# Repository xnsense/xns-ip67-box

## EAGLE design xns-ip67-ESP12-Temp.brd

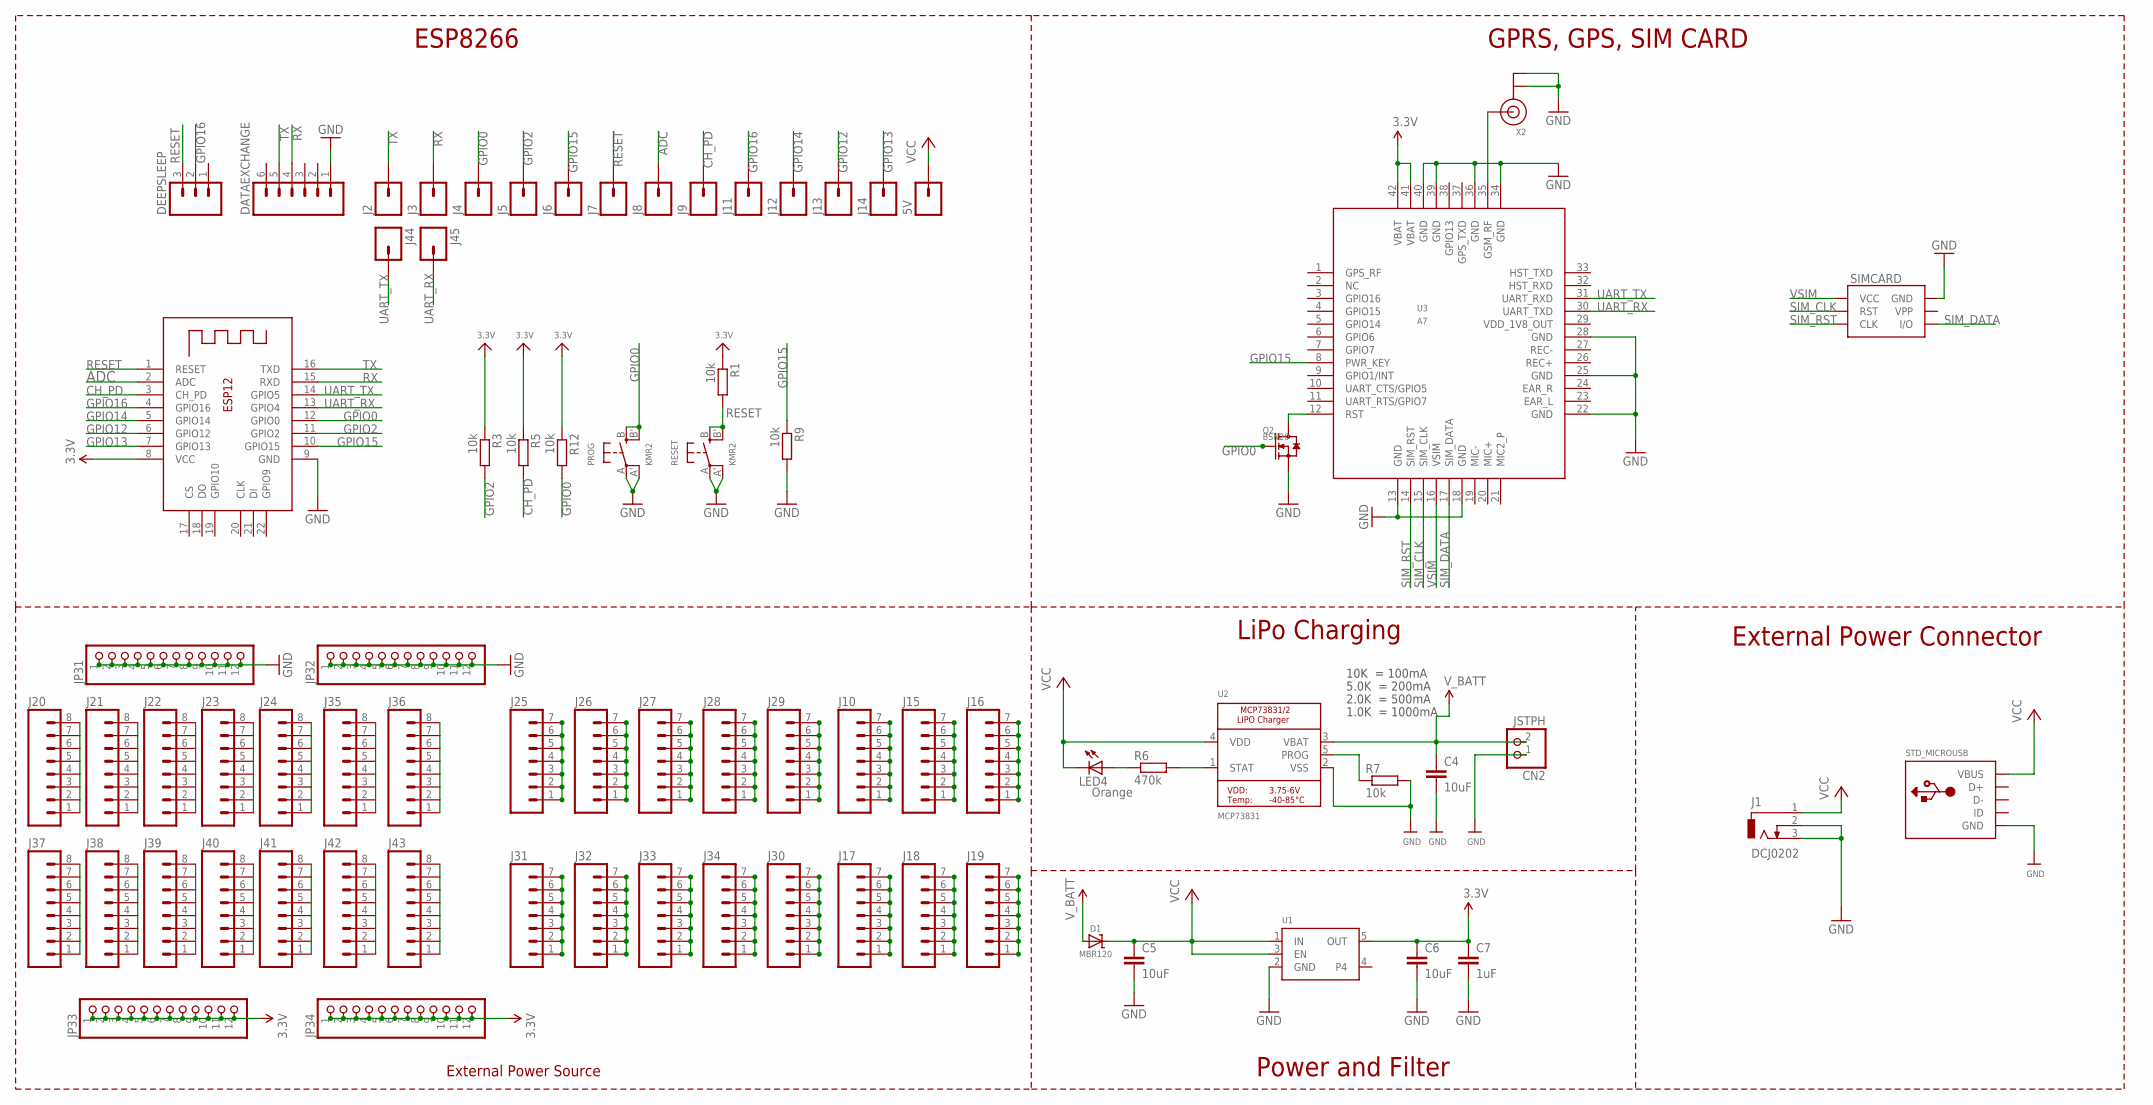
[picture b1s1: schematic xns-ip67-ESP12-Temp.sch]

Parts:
5V: M01NOSILK-KIT; 1X01NS-KIT
C4, C5, C6: 10uF; C2.5-2
C7: 1uF; C2.5-2
CN2: JSTPH; JSTPH2
D1: MBR120; SOD-123
DATAEXCHANGE: M06FEMALE_LOCK; 1X06_FEMALE_LOCK.010
DEEPSLEEP: M031X03_NO_SILK; 1X03_NO_SILK
J1: DCJ0202
J2, J3, J4, J5, J6, J7, J8, J9, J11, J12, J13, J14, J44, J45: M01NOSILK-KIT; 1X01NS-KIT
J10, J15, J16, J17, J18, J19, J25, J26, J27, J28, J29, J30, J31, J32, J33, J34: M07NO_SILK; 1X07_NO_SILK
J20, J21, J22, J23, J24, J35, J36, J37, J38, J39, J40, J41, J42, J43: M08NO_SILK_FEMALE_PTH; 1X08_NO_SILK
JP31, JP32, JP33, JP34: HEADER-1X12; 1X12_ROUND
LED4: Orange; LED5MM
PROG: KMR2; BTN_KMR2_4.6X2.8
Q2: BSN20; SOT23@1
R1, R3, R5, R7, R9, R12: 10k; 0204/7
R6: 470k; 0204/7
RESET: KMR2; BTN_KMR2_4.6X2.8
SIMCARD: SIMHOLDERSIM; SIMHOLDER
STD_MICROUSB: USB_MICRO_20329_V2; 4UCONN_20329_V2
U1: VREG_SOT23-5; SOT23-5
U2: MCP73831; SOT23-5@1
U3: A7
X1: ESP-12E
X2: ANTENNA_U.FL; U.FL

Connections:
3.3V: C6.1, C7.1, JP33.1, JP33.2, JP33.3, JP33.4, JP33.5, JP33.6, JP33.7, JP33.8, JP33.9, JP33.10, JP33.11, JP33.12, JP34.1, JP34.2, JP34.3, JP34.4, JP34.5, JP34.6, JP34.7, JP34.8, JP34.9, JP34.10, JP34.11, JP34.12, R1.1, R3.1, R5.1, R12.1, U1.5 (OUT), U3.41 (VBAT), U3.42 (VBAT), X1.8 (VCC)
ADC: J8.1, X1.2 (ADC)
CH_PD: J9.1, R5.2, X1.3 (CH_PD)
GND: C4.2, C5.2, C6.2, C7.2, CN2.1, DATAEXCHANGE.1, J1.2, J1.3, JP31.1, JP31.2, JP31.3, JP31.4, JP31.5, JP31.6, JP31.7, JP31.8, JP31.9, JP31.10, JP31.11, JP31.12, JP32.1, JP32.2, JP32.3, JP32.4, JP32.5, JP32.6, JP32.7, JP32.8, JP32.9, JP32.10, JP32.11, JP32.12, PROG.A, PROG.A' (P1), Q2.2 (S), R7.2, R9.2, RESET.A, RESET.A' (P1), SIMCARD.C5 (GND), STD_MICROUSB.BASE@1 (GND), STD_MICROUSB.BASE@2 (GND), STD_MICROUSB.GND, STD_MICROUSB.SPRT@1 (GND), STD_MICROUSB.SPRT@2 (GND), STD_MICROUSB.SPRT@3 (GND), STD_MICROUSB.SPRT@4 (GND), U1.2 (GND), U2.2 (VSS), U3.13 (GND), U3.18 (GND), U3.22 (GND), U3.25 (GND), U3.28 (GND), U3.34 (GND), U3.36 (GND), U3.39 (GND), U3.40 (GND), X1.9 (GND), X2.1 (GND), X2.2 (GND)
GPIO0: J4.1, PROG.B (S), PROG.B' (S1), Q2.1 (G), R12.2, X1.12 (GPIO0)
GPIO2: J5.1, R3.2, X1.11 (GPIO2)
GPIO12: J13.1, X1.6 (GPIO12)
GPIO13: J14.1, X1.7 (GPIO13)
GPIO14: J12.1, X1.5 (GPIO14)
GPIO15: J6.1, R9.1, U3.8 (PWR_KEY), X1.10 (GPIO15)
GPIO16: DEEPSLEEP.2, J11.1, X1.4 (GPIO16)
unnamed: J20.1, J20.2, J20.3, J20.4, J20.5, J20.6, J20.7, J20.8
unnamed: J21.1, J21.2, J21.3, J21.4, J21.5, J21.6, J21.7, J21.8
unnamed: U3.35 (GSM_RF), X2.3 (SIGNAL)
unnamed: J22.1, J22.2, J22.3, J22.4, J22.5, J22.6, J22.7, J22.8
unnamed: J23.1, J23.2, J23.3, J23.4, J23.5, J23.6, J23.7, J23.8
unnamed: J24.1, J24.2, J24.3, J24.4, J24.5, J24.6, J24.7, J24.8
unnamed: J35.1, J35.2, J35.3, J35.4, J35.5, J35.6, J35.7, J35.8
unnamed: J37.1, J37.2, J37.3, J37.4, J37.5, J37.6, J37.7, J37.8
unnamed: J38.1, J38.2, J38.3, J38.4, J38.5, J38.6, J38.7, J38.8
unnamed: J39.1, J39.2, J39.3, J39.4, J39.5, J39.6, J39.7, J39.8
unnamed: J40.1, J40.2, J40.3, J40.4, J40.5, J40.6, J40.7, J40.8
unnamed: J10.1, J10.2, J10.3, J10.4, J10.5, J10.6, J10.7
unnamed: J41.1, J41.2, J41.3, J41.4, J41.5, J41.6, J41.7, J41.8
unnamed: J15.1, J15.2, J15.3, J15.4, J15.5, J15.6, J15.7
unnamed: J16.1, J16.2, J16.3, J16.4, J16.5, J16.6, J16.7
unnamed: J17.1, J17.2, J17.3, J17.4, J17.5, J17.6, J17.7
unnamed: J18.1, J18.2, J18.3, J18.4, J18.5, J18.6, J18.7
unnamed: J19.1, J19.2, J19.3, J19.4, J19.5, J19.6, J19.7
unnamed: J42.1, J42.2, J42.3, J42.4, J42.5, J42.6, J42.7, J42.8
unnamed: J36.1, J36.2, J36.3, J36.4, J36.5, J36.6, J36.7, J36.8
unnamed: J43.1, J43.2, J43.3, J43.4, J43.5, J43.6, J43.7, J43.8
unnamed: R7.1, U2.5 (PROG)
unnamed: J31.1, J31.2, J31.3, J31.4, J31.5, J31.6, J31.7
unnamed: J32.1, J32.2, J32.3, J32.4, J32.5, J32.6, J32.7
unnamed: R6.2, U2.1 (STAT)
unnamed: J33.1, J33.2, J33.3, J33.4, J33.5, J33.6, J33.7
unnamed: J34.1, J34.2, J34.3, J34.4, J34.5, J34.6, J34.7
unnamed: LED4.A, R6.1
unnamed: J25.1, J25.2, J25.3, J25.4, J25.5, J25.6, J25.7
unnamed: J26.1, J26.2, J26.3, J26.4, J26.5, J26.6, J26.7
unnamed: J27.1, J27.2, J27.3, J27.4, J27.5, J27.6, J27.7
unnamed: J28.1, J28.2, J28.3, J28.4, J28.5, J28.6, J28.7
unnamed: J29.1, J29.2, J29.3, J29.4, J29.5, J29.6, J29.7
unnamed: J30.1, J30.2, J30.3, J30.4, J30.5, J30.6, J30.7
RESET: DEEPSLEEP.3, J7.1, R1.2, RESET.B (S), RESET.B' (S1), X1.1 (RESET)
RESET_KEY: Q2.3 (D), U3.12 (RST)
RX: DATAEXCHANGE.4, J3.1, X1.15 (RXD)
SIM_CLK: SIMCARD.C2 (RST), U3.15 (SIM_CLK)
SIM_DATA: SIMCARD.C7 (I/O), U3.17 (SIM_DATA)
SIM_RST: SIMCARD.C3 (CLK), U3.14 (SIM_RST)
TX: DATAEXCHANGE.5, J2.1, X1.16 (TXD)
UART_RX: J45.1, U3.30 (UART_TXD), X1.13 (GPIO4)
UART_TX: J44.1, U3.31 (UART_RXD), X1.14 (GPIO5)
VCC: 5V.1, C5.1, D1.C, J1.1, LED4.K (C), STD_MICROUSB.VBUS, U1.1 (IN), U1.3 (EN), U2.4 (VDD)
VSIM: SIMCARD.C1 (VCC), U3.16 (VSIM)
V_BATT: C4.1, CN2.2, D1.A, U2.3 (VBAT)

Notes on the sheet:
10K = 100mA
5.0K = 200mA
2.0K = 500mA
1.0K = 1000mA
External Power Connector
LiPo Charging
Power and Filter
GPRS, GPS, SIM CARD
ESP8266
External Power Source

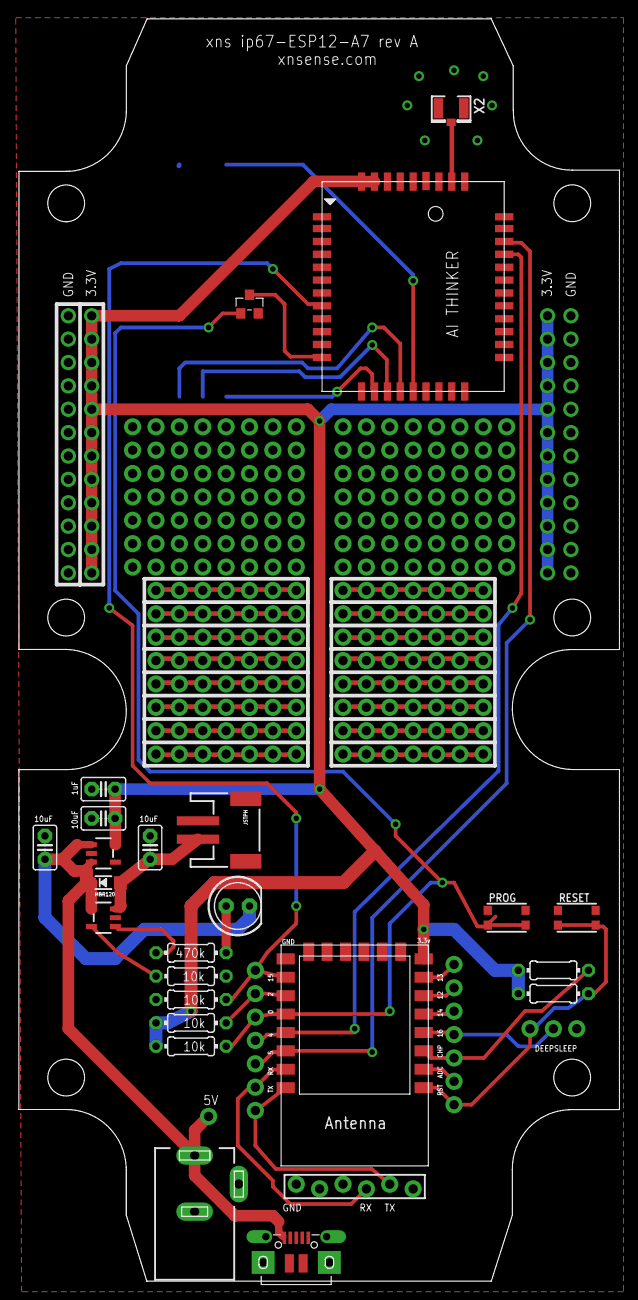
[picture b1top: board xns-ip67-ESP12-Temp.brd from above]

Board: 2 copper layers, 65.3 x 137.2 mm, 76 parts (1 on the bottom side), 57 nets.

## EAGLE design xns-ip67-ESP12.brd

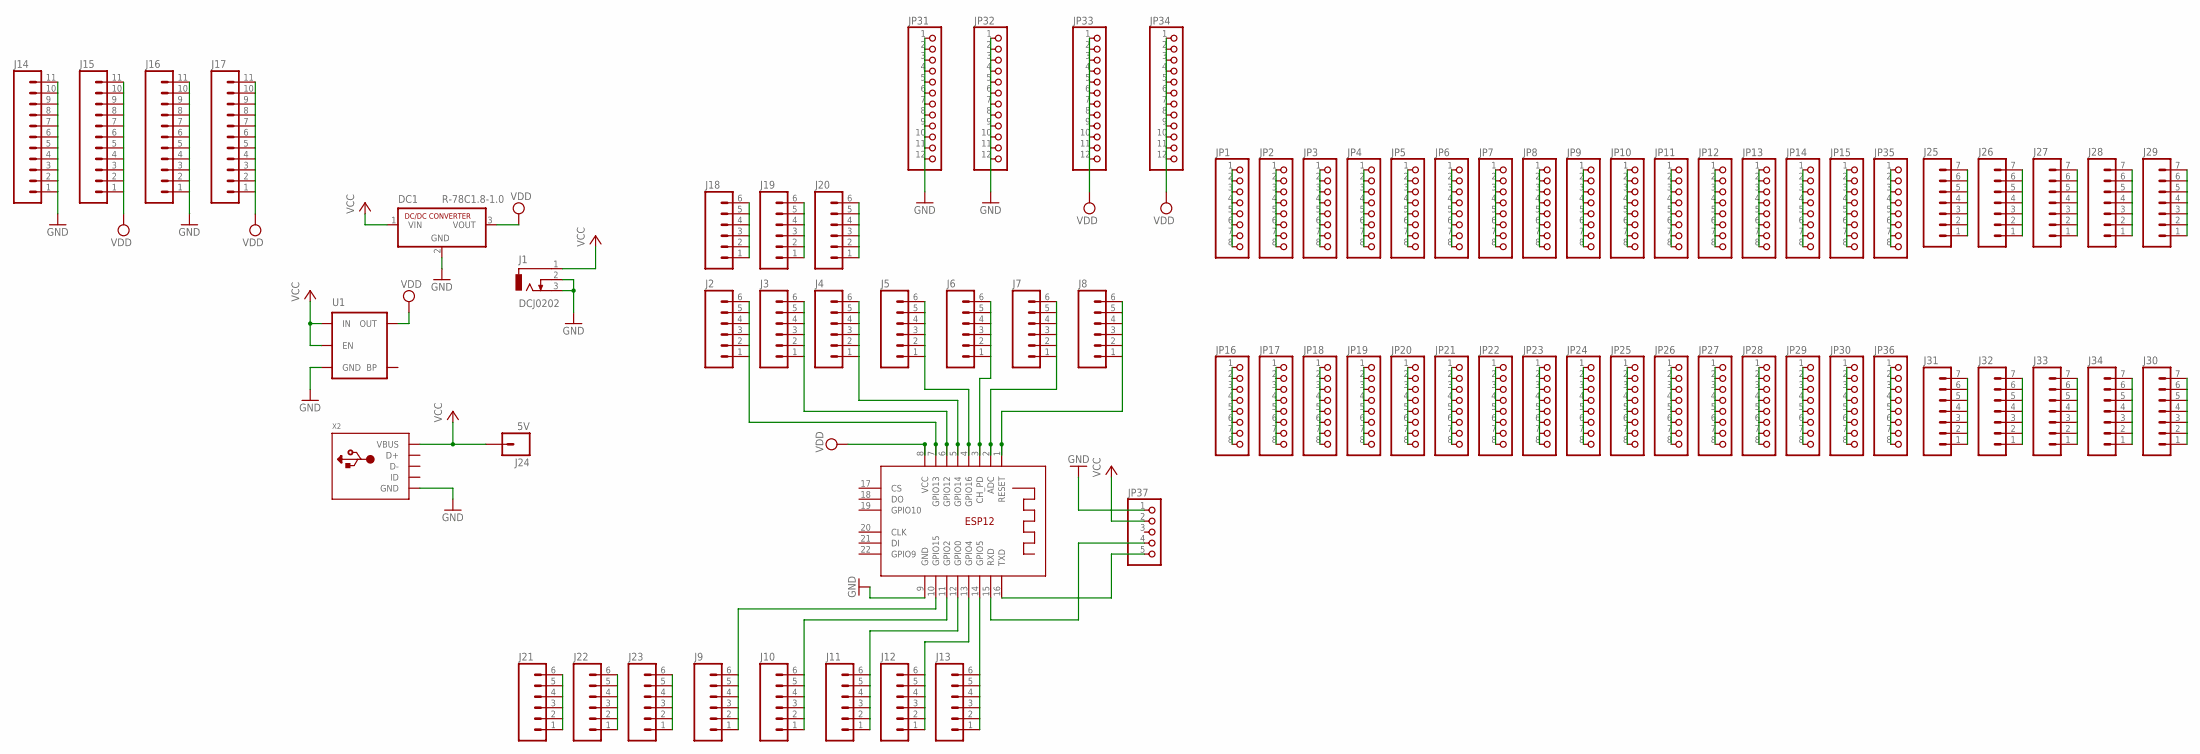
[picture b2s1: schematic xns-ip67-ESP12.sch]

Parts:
DC1: R-78C1.8-1.0; SIP3
J1: DCJ0202
J2, J3, J4, J5, J6, J7, J8, J9, J10, J11, J12, J13, J18, J19, J20, J21, J22, J23: M06NO_SILK_FEMALE_PTH; 1X06_NO_SILK
J14, J15, J16, J17: M111X11_NO_SILK; 1X11_NO_SILK
J24: 5V; 1X01_NO_SILK
J25, J26, J27, J28, J29, J30, J31, J32, J33, J34: M07NO_SILK; 1X07_NO_SILK
JP1, JP2, JP3, JP4, JP5, JP6, JP7, JP8, JP9, JP10, JP11, JP12, JP13, JP14, JP15, JP16, JP17, JP18, JP19, JP20, JP21, JP22, JP23, JP24, JP25, JP26, JP27, JP28, JP29, JP30, JP35, JP36: PINHD-1X8CLEANBIG; 1X08-CLEANBIG
JP31, JP32, JP33, JP34: HEADER-1X12; 1X12_ROUND
JP37: PINHD-1X5; 1X05
U1: MIC52053.3V; SOT23-5
X1: ESP-12E
X2: USBMICRO_20329; 4UCONN_20329

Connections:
GND: DC1.2 (GND), J1.2, J1.3, J14.1, J14.2, J14.3, J14.4, J14.5, J14.6, J14.7, J14.8, J14.9, J14.10, J14.11, J16.1, J16.2, J16.3, J16.4, J16.5, J16.6, J16.7, J16.8, J16.9, J16.10, J16.11, JP31.1, JP31.2, JP31.3, JP31.4, JP31.5, JP31.6, JP31.7, JP31.8, JP31.9, JP31.10, JP31.11, JP31.12, JP32.1, JP32.2, JP32.3, JP32.4, JP32.5, JP32.6, JP32.7, JP32.8, JP32.9, JP32.10, JP32.11, JP32.12, JP37.1, U1.2 (GND), X1.9 (GND), X2.BASE@1 (GND), X2.BASE@2 (GND), X2.GND, X2.SPRT@1 (GND), X2.SPRT@2 (GND), X2.SPRT@3 (GND), X2.SPRT@4 (GND)
unnamed: J2.1, J2.2, J2.3, J2.4, J2.5, J2.6, X1.7 (GPIO13)
unnamed: J3.1, J3.2, J3.3, J3.4, J3.5, J3.6, X1.6 (GPIO12)
unnamed: J4.1, J4.2, J4.3, J4.4, J4.5, J4.6, X1.5 (GPIO14)
unnamed: JP37.5, X1.16 (TXD)
unnamed: J5.1, J5.2, J5.3, J5.4, J5.5, J5.6, X1.4 (GPIO16)
unnamed: J6.1, J6.2, J6.3, J6.4, J6.5, J6.6, X1.3 (CH_PD)
unnamed: JP23.1, JP23.2, JP23.3, JP23.4, JP23.5, JP23.6, JP23.7, JP23.8
unnamed: J7.1, J7.2, J7.3, J7.4, J7.5, J7.6, X1.2 (ADC)
unnamed: J8.1, J8.2, J8.3, J8.4, J8.5, J8.6, X1.1 (RESET)
unnamed: J9.1, J9.2, J9.3, J9.4, J9.5, J9.6, X1.10 (GPIO15)
unnamed: J10.1, J10.2, J10.3, J10.4, J10.5, J10.6, X1.11 (GPIO2)
unnamed: J11.1, J11.2, J11.3, J11.4, J11.5, J11.6, X1.12 (GPIO0)
unnamed: JP37.4, X1.15 (RXD)
unnamed: J12.1, J12.2, J12.3, J12.4, J12.5, J12.6, X1.13 (GPIO4)
unnamed: J13.1, J13.2, J13.3, J13.4, J13.5, J13.6, X1.14 (GPIO5)
unnamed: J18.1, J18.2, J18.3, J18.4, J18.5, J18.6
unnamed: J19.1, J19.2, J19.3, J19.4, J19.5, J19.6
unnamed: J20.1, J20.2, J20.3, J20.4, J20.5, J20.6
unnamed: J21.1, J21.2, J21.3, J21.4, J21.5, J21.6
unnamed: J22.1, J22.2, J22.3, J22.4, J22.5, J22.6
unnamed: JP1.1, JP1.2, JP1.3, JP1.4, JP1.5, JP1.6, JP1.7, JP1.8
unnamed: JP2.1, JP2.2, JP2.3, JP2.4, JP2.5, JP2.6, JP2.7, JP2.8
unnamed: JP3.1, JP3.2, JP3.3, JP3.4, JP3.5, JP3.6, JP3.7, JP3.8
unnamed: JP4.1, JP4.2, JP4.3, JP4.4, JP4.5, JP4.6, JP4.7, JP4.8
unnamed: JP5.1, JP5.2, JP5.3, JP5.4, JP5.5, JP5.6, JP5.7, JP5.8
unnamed: JP6.1, JP6.2, JP6.3, JP6.4, JP6.5, JP6.6, JP6.7, JP6.8
unnamed: JP7.1, JP7.2, JP7.3, JP7.4, JP7.5, JP7.6, JP7.7, JP7.8
unnamed: JP8.1, JP8.2, JP8.3, JP8.4, JP8.5, JP8.6, JP8.7, JP8.8
unnamed: JP9.1, JP9.2, JP9.3, JP9.4, JP9.5, JP9.6, JP9.7, JP9.8
unnamed: JP10.1, JP10.2, JP10.3, JP10.4, JP10.5, JP10.6, JP10.7, JP10.8
unnamed: JP11.1, JP11.2, JP11.3, JP11.4, JP11.5, JP11.6, JP11.7, JP11.8
unnamed: JP12.1, JP12.2, JP12.3, JP12.4, JP12.5, JP12.6, JP12.7, JP12.8
unnamed: JP13.1, JP13.2, JP13.3, JP13.4, JP13.5, JP13.6, JP13.7, JP13.8
unnamed: JP14.1, JP14.2, JP14.3, JP14.4, JP14.5, JP14.6, JP14.7, JP14.8
unnamed: JP15.1, JP15.2, JP15.3, JP15.4, JP15.5, JP15.6, JP15.7, JP15.8
unnamed: JP30.1, JP30.2, JP30.3, JP30.4, JP30.5, JP30.6, JP30.7, JP30.8
unnamed: JP29.1, JP29.2, JP29.3, JP29.4, JP29.5, JP29.6, JP29.7, JP29.8
unnamed: JP28.1, JP28.2, JP28.3, JP28.4, JP28.5, JP28.6, JP28.7, JP28.8
unnamed: JP27.1, JP27.2, JP27.3, JP27.4, JP27.5, JP27.6, JP27.7, JP27.8
unnamed: JP26.1, JP26.2, JP26.3, JP26.4, JP26.5, JP26.6, JP26.7, JP26.8
unnamed: JP25.1, JP25.2, JP25.3, JP25.4, JP25.5, JP25.6, JP25.7, JP25.8
unnamed: JP24.1, JP24.2, JP24.3, JP24.4, JP24.5, JP24.6, JP24.7, JP24.8
unnamed: JP22.1, JP22.2, JP22.3, JP22.4, JP22.5, JP22.6, JP22.7, JP22.8
unnamed: JP21.1, JP21.2, JP21.3, JP21.4, JP21.5, JP21.6, JP21.7, JP21.8
unnamed: JP20.1, JP20.2, JP20.3, JP20.4, JP20.5, JP20.6, JP20.7, JP20.8
unnamed: JP19.1, JP19.2, JP19.3, JP19.4, JP19.5, JP19.6, JP19.7, JP19.8
unnamed: JP18.1, JP18.2, JP18.3, JP18.4, JP18.5, JP18.6, JP18.7, JP18.8
unnamed: JP17.1, JP17.2, JP17.3, JP17.4, JP17.5, JP17.6, JP17.7, JP17.8
unnamed: JP16.1, JP16.2, JP16.3, JP16.4, JP16.5, JP16.6, JP16.7, JP16.8
unnamed: JP35.1, JP35.2, JP35.3, JP35.4, JP35.5, JP35.6, JP35.7, JP35.8
unnamed: JP36.1, JP36.2, JP36.3, JP36.4, JP36.5, JP36.6, JP36.7, JP36.8
unnamed: J31.1, J31.2, J31.3, J31.4, J31.5, J31.6, J31.7
unnamed: J32.1, J32.2, J32.3, J32.4, J32.5, J32.6, J32.7
unnamed: J33.1, J33.2, J33.3, J33.4, J33.5, J33.6, J33.7
unnamed: J34.1, J34.2, J34.3, J34.4, J34.5, J34.6, J34.7
unnamed: J23.1, J23.2, J23.3, J23.4, J23.5, J23.6
unnamed: J25.1, J25.2, J25.3, J25.4, J25.5, J25.6, J25.7
unnamed: J26.1, J26.2, J26.3, J26.4, J26.5, J26.6, J26.7
unnamed: J27.1, J27.2, J27.3, J27.4, J27.5, J27.6, J27.7
unnamed: J28.1, J28.2, J28.3, J28.4, J28.5, J28.6, J28.7
unnamed: J29.1, J29.2, J29.3, J29.4, J29.5, J29.6, J29.7
unnamed: J30.1, J30.2, J30.3, J30.4, J30.5, J30.6, J30.7
VCC: DC1.1 (VIN), J1.1, J24.1, JP37.2, U1.1 (IN), U1.3 (EN), X2.VBUS
VDD: DC1.3 (VOUT), J15.1, J15.2, J15.3, J15.4, J15.5, J15.6, J15.7, J15.8, J15.9, J15.10, J15.11, J17.1, J17.2, J17.3, J17.4, J17.5, J17.6, J17.7, J17.8, J17.9, J17.10, J17.11, JP33.1, JP33.2, JP33.3, JP33.4, JP33.5, JP33.6, JP33.7, JP33.8, JP33.9, JP33.10, JP33.11, JP33.12, JP34.1, JP34.2, JP34.3, JP34.4, JP34.5, JP34.6, JP34.7, JP34.8, JP34.9, JP34.10, JP34.11, JP34.12, U1.5 (OUT), X1.8 (VCC)

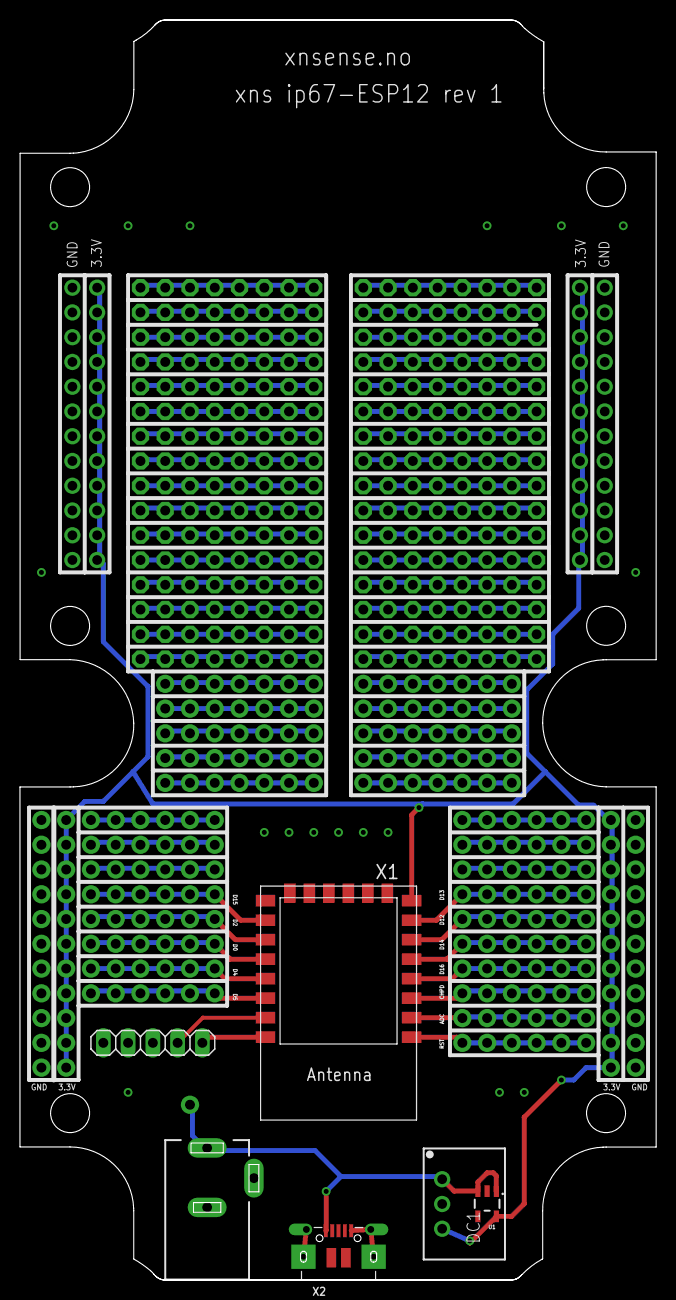
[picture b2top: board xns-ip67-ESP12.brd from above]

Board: 2 copper layers, 65.3 x 129.3 mm, 75 parts (0 on the bottom side), 65 nets.

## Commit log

2016-11-18 Init
    First commit
2016-11-20 Rev 0
    First Version without routing
2016-11-20 Rev 0 Autoroute
    Rev 0 with Autoroute
2016-11-21 New route
    reroute
2016-11-23 Updated design
    Added more wire pads on side of ESP
2016-11-23 Updated routes
    Added missed GND routes on USB
2016-11-23 Change FTDI Header
    Change FTDI Header
2016-11-23 Updated gitignore
2016-11-23 Updates
    Gerb files and Name update
2016-11-23 Deleted pro file
2016-11-23 Gerb zip
    Zipped Gerb files
2017-01-08 Version without esp8266
    Simple version
2017-01-09 Routed and Gerb files
    Routed and produced verb files
2017-01-10 board fix
    small fix
2017-01-20 New board layout
    New board layout
2017-01-22 Change square via to round
    Change square via to round
2017-01-24 Board dimension changes
    Adjusted to be edge to edge
2017-01-27 Added LiPo charging (new)
    Components are not aligned etc, just added based on feather board. No
    other components has been removed.
2017-02-08 Remove git crap that was added in last commit
    Fix files
2017-03-01 ip67 version with A7, SIM, SMA
    Test version with A7, SIM Card Holder and SMA Antenna
2017-03-07 More stuff
    ff
2017-03-13 New board for Temp
    New board for Temp logging with A7, Power lines is routed
2017-03-17 Eagle Upgrade, Routing finished alpha
2017-03-17 Cleanup, add PIN's
    Added Pin for GPIO’s

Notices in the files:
parts and their libraries:
SparkFun-Connectors: Licensing: Creative Commons ShareAlike 4.0 International - https://creativecommons.org/licenses/by-sa/4.0
